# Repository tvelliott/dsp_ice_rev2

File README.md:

<html>
<b>480 MHz STM32H743 + ICE40 8K FGPA development board with 10/100 Ethernet interface 
<BR>
<BR><B>DSP_ICE_REV2
<BR>
<p>

<BR>
<BR>
Features
<BR>
<BR>
<PRE>
16-bit FSMC Interface between MCU <> FPGA  (DMA is supported)
3.5mm audio jack with high quality I2S DAC.  I2S can be generated from FPGA or MCU
FPGA clock input / PLL is fed from MCU MC0 output
Low Noise 3.3V supply
4 PMOD-style ports with 3.3V or 5V selectable voltages
10/100 Mbps Ethernet Interface  (DMA supported,  90+ Mbps IPerf results)
PDM Microphone connected to FPGA
</PRE>
  
<BR><BR>If you are looking for something similar, but with firmware / HDL code already available,  take a look at DSP_ICE Rev 1 here
<BR>https://github.com/tvelliott/dsp_ice 
</html>

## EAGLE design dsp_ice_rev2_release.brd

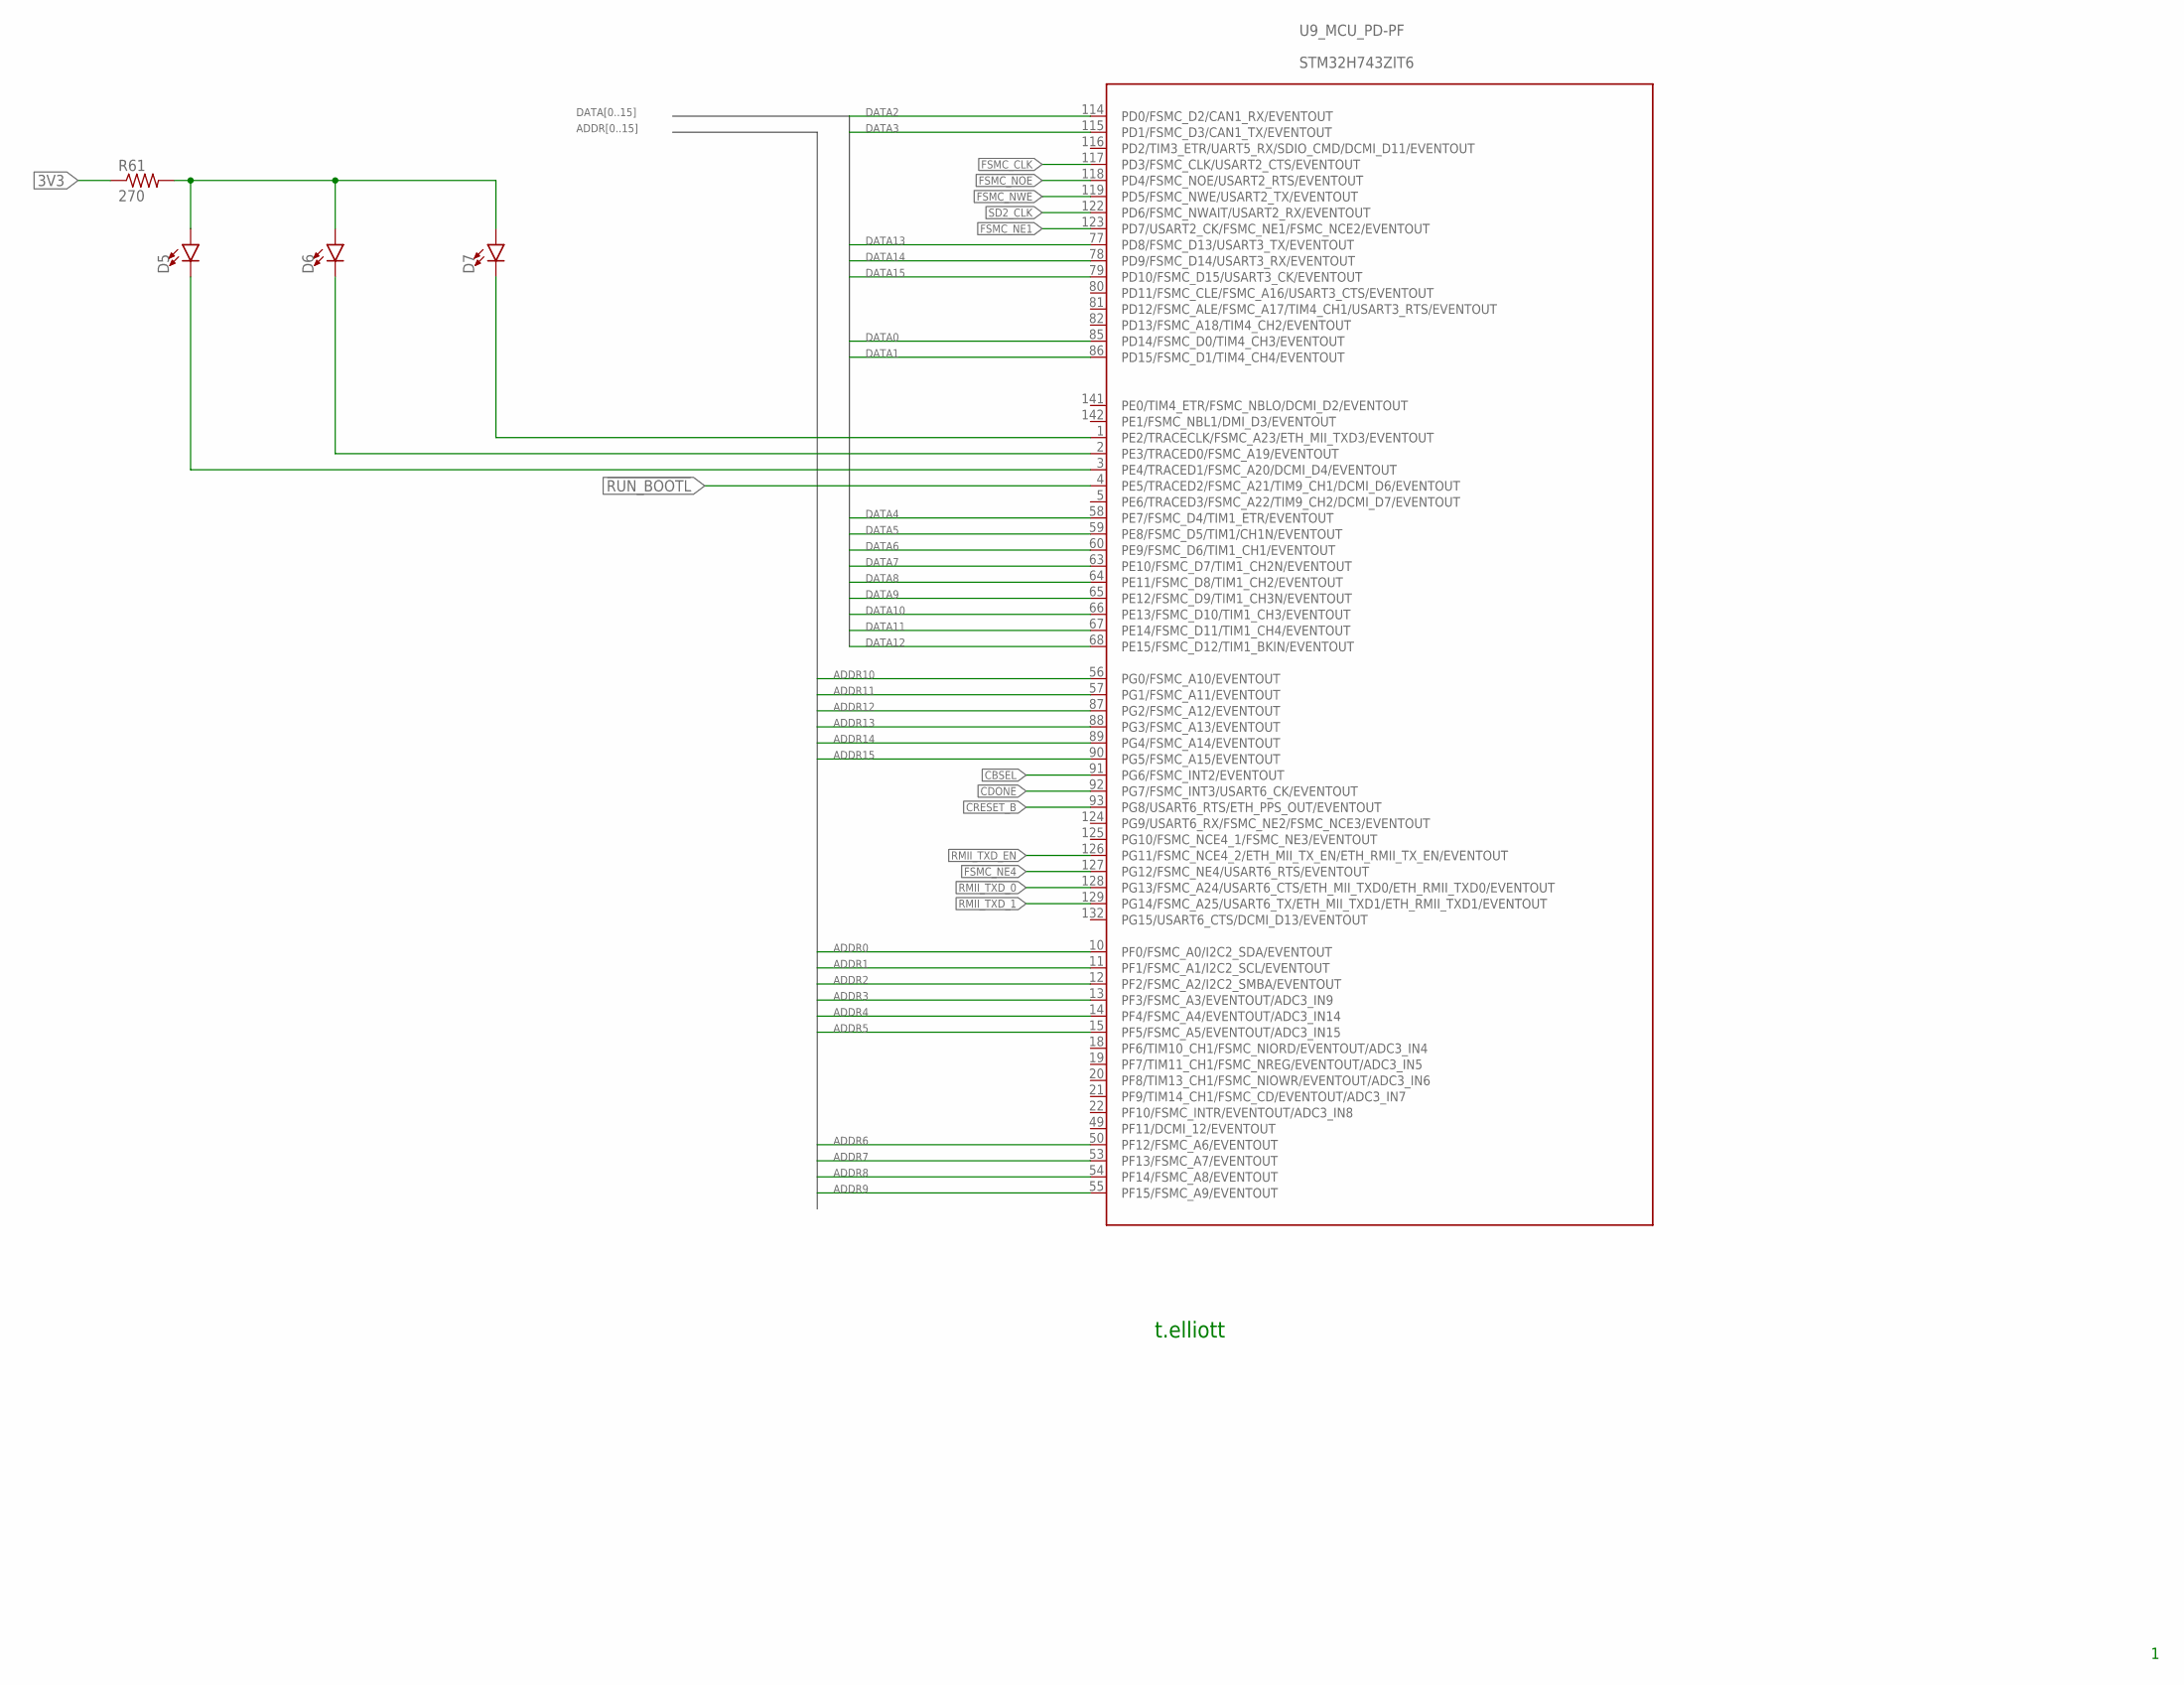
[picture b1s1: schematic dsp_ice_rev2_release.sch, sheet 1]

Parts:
D5, D6, D7: LED1206; LED-1206
R61: 270; R0603
U9: STM32H743ZIT6; STM32F407_144

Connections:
3V3: R61.1; also elsewhere on the board
!RUN_BOOTL: U9.4 (PE5/TRACED2/FSMC_A21/TIM9_CH1/DCMI_D6/E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); also elsewhere on the board
ADDR0: U9.10 (PF0/FSMC_A0/I2C2_SDA/EVENTOUT); also elsewhere on the board
ADDR1: U9.11 (PF1/FSMC_A1/I2C2_SCL/EVENTOUT); also elsewhere on the board
ADDR2: U9.12 (PF2/FSMC_A2/I2C2_SMBA/EVENTOUT); also elsewhere on the board
ADDR3: U9.13 (PF3/FSMC_A3/EVENTOUT/ADC3_IN9); also elsewhere on the board
ADDR4: U9.14 (PF4/FSMC_A4/EVENTOUT/ADC3_IN14); also elsewhere on the board
ADDR5: U9.15 (PF5/FSMC_A5/EVENTOUT/ADC3_IN15); also elsewhere on the board
ADDR6: U9.50 (PF12/FSMC_A6/EVENTOUT); also elsewhere on the board
ADDR7: U9.53 (PF13/FSMC_A7/EVENTOUT); also elsewhere on the board
ADDR8: U9.54 (PF14/FSMC_A8/EVENTOUT); also elsewhere on the board
ADDR9: U9.55 (PF15/FSMC_A9/EVENTOUT); also elsewhere on the board
ADDR10: U9.56 (PG0/FSMC_A10/EVENTOUT); also elsewhere on the board
ADDR11: U9.57 (PG1/FSMC_A11/EVENTOUT); also elsewhere on the board
ADDR12: U9.87 (PG2/FSMC_A12/EVENTOUT); also elsewhere on the board
ADDR13: U9.88 (PG3/FSMC_A13/EVENTOUT); also elsewhere on the board
ADDR14: U9.89 (PG4/FSMC_A14/EVENTOUT); also elsewhere on the board
ADDR15: U9.90 (PG5/FSMC_A15/EVENTOUT); also elsewhere on the board
CBSEL: U9.91 (PG6/FSMC_INT2/EVENTOUT); also elsewhere on the board
CDONE: U9.92 (PG7/FSMC_INT3/USART6_CK/EVENTOUT); also elsewhere on the board
CRESET_B: U9.93 (PG8/USART6_RTS/ETH_PPS_OUT/EVENTOUT); also elsewhere on the board
DATA0: U9.85 (PD14/FSMC_D0/TIM4_CH3/EVENTOUT); also elsewhere on the board
DATA1: U9.86 (PD15/FSMC_D1/TIM4_CH4/EVENTOUT); also elsewhere on the board
DATA2: U9.114 (PD0/FSMC_D2/CAN1_RX/EVENTOUT); also elsewhere on the board
DATA3: U9.115 (PD1/FSMC_D3/CAN1_TX/EVENTOUT); also elsewhere on the board
DATA4: U9.58 (PE7/FSMC_D4/TIM1_ETR/EVENTOUT); also elsewhere on the board
DATA5: U9.59 (PE8/FSMC_D5/TIM1/CH1N/EVENTOUT); also elsewhere on the board
DATA6: U9.60 (PE9/FSMC_D6/TIM1_CH1/EVENTOUT); also elsewhere on the board
DATA7: U9.63 (PE10/FSMC_D7/TIM1_CH2N/EVENTOUT); also elsewhere on the board
DATA8: U9.64 (PE11/FSMC_D8/TIM1_CH2/EVENTOUT); also elsewhere on the board
DATA9: U9.65 (PE12/FSMC_D9/TIM1_CH3N/EVENTOUT); also elsewhere on the board
DATA10: U9.66 (PE13/FSMC_D10/TIM1_CH3/EVENTOUT); also elsewhere on the board
DATA11: U9.67 (PE14/FSMC_D11/TIM1_CH4/EVENTOUT); also elsewhere on the board
DATA12: U9.68 (PE15/FSMC_D12/TIM1_BKIN/EVENTOUT); also elsewhere on the board
DATA13: U9.77 (PD8/FSMC_D13/USART3_TX/EVENTOUT); also elsewhere on the board
DATA14: U9.78 (PD9/FSMC_D14/USART3_RX/EVENTOUT); also elsewhere on the board
DATA15: U9.79 (PD10/FSMC_D15/USART3_CK/EVENTOUT); also elsewhere on the board
FSMC_CLK: U9.117 (PD3/FSMC_CLK/USART2_CTS/EVENTOUT); also elsewhere on the board
FSMC_NE1: U9.123 (PD7/USART2_CK/FSMC_NE1/FSMC_NCE2/EVENTO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); also elsewhere on the board
FSMC_NE4: U9.127 (PG12/FSMC_NE4/USART6_RTS/EVENTOUT); also elsewhere on the board
FSMC_NOE: U9.118 (PD4/FSMC_NOE/USART2_RTS/EVENTOUT); also elsewhere on the board
FSMC_NWE: U9.119 (PD5/FSMC_NWE/USART2_TX/EVENTOUT); also elsewhere on the board
unnamed: D5.A, D6.A, D7.A, R61.2
unnamed: D7.C, U9.1 (PE2/TRACECLK/FSMC_A23/ETH_MII_TXD3/EVEN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)
unnamed: D6.C, U9.2 (PE3/TRACED0/FSMC_A19/EVENTOUT)
unnamed: D5.C, U9.3 (PE4/TRACED1/FSMC_A20/DCMI_D4/EVENTOUT)
RMII_TXD_0: U9.128 (PG13/FSMC_A24/USART6_CTS/ETH_MII_TXD0/E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); also elsewhere on the board
RMII_TXD_1: U9.129 (PG14/FSMC_A25/USART6_TX/ETH_MII_TXD1/ET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); also elsewhere on the board
RMII_TXD_EN: U9.126 (PG11/FSMC_NCE4_2/ETH_MII_TX_EN/ETH_RMII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); also elsewhere on the board
SD2_CLK: U9.122 (PD6/FSMC_NWAIT/USART2_RX/EVENTOUT); also elsewhere on the board

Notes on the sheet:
t.elliott

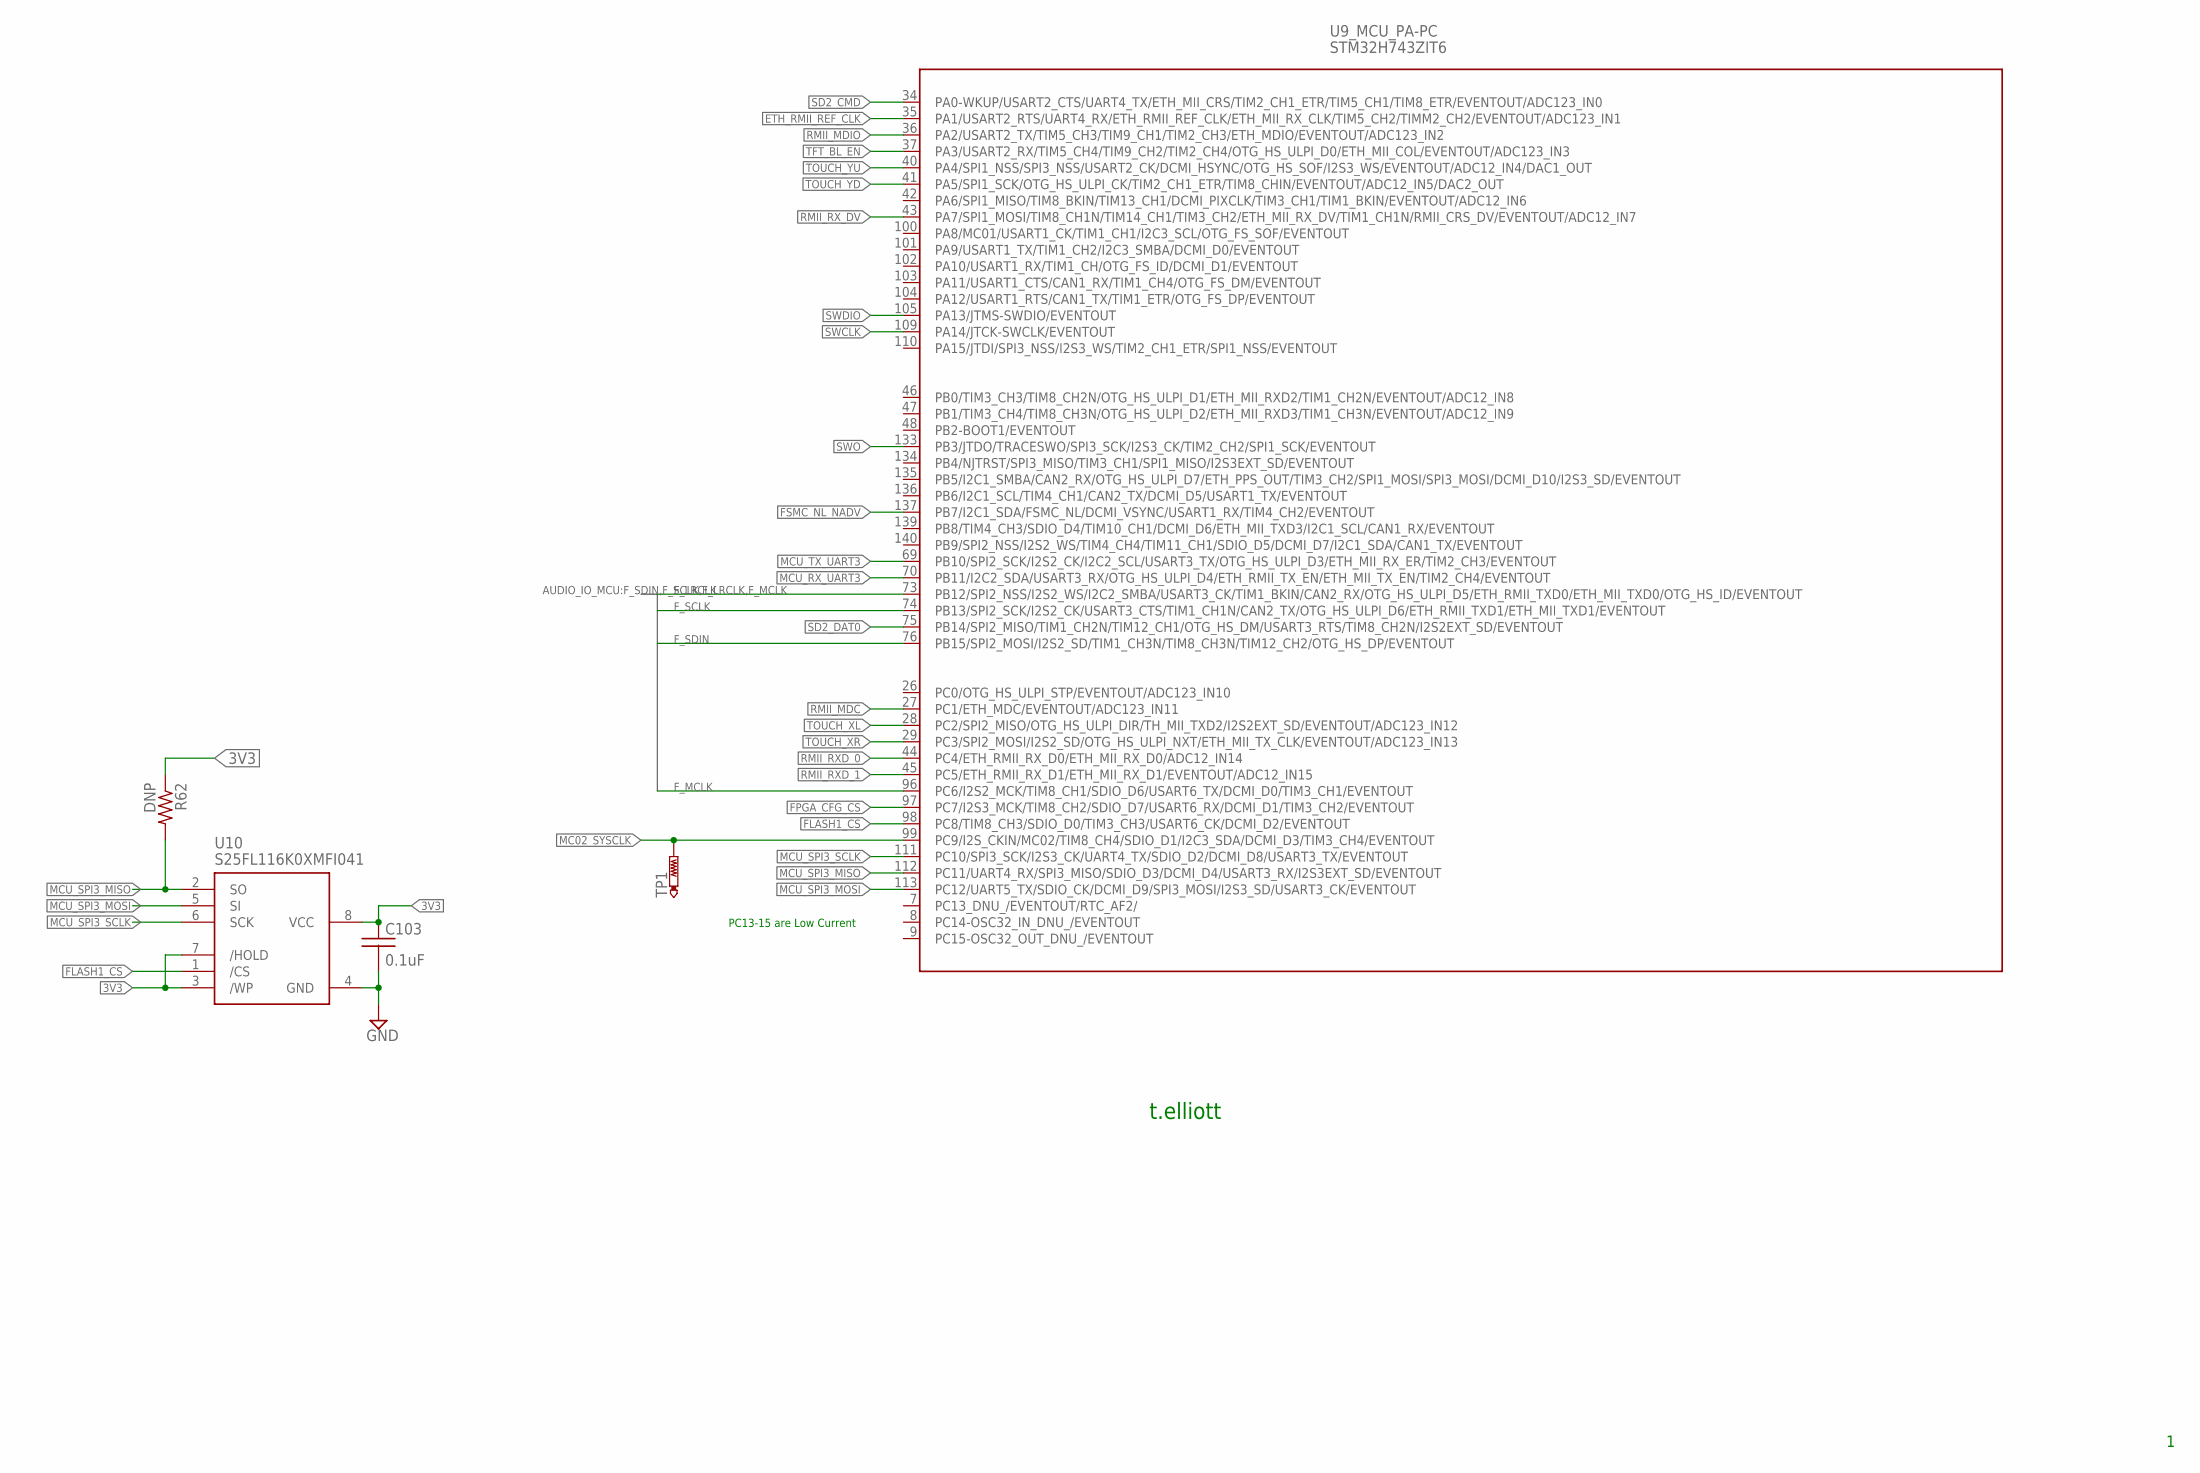
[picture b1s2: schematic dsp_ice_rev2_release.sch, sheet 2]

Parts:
C103: 0.1uF; C0603
R62: DNP; R0603
TP1: PTR1TP08R; TP08R
U9: STM32H743ZIT6; STM32F407_144
U10: S25FL116K0XMFI041; SO8

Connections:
3V3: C103.1, R62.1, U10.3 (/WP), U10.7 (/HOLD), U10.8 (VCC); also elsewhere on the board
ETH_RMII_REF_CLK: U9.35 (PA1/USART2_RTS/UART4_RX/ETH_RMII_REF_CL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); also elsewhere on the board
FLASH1_CS: U9.98 (PC8/TIM8_CH3/SDIO_D0/TIM3_CH3/USART6_CK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), U10.1 (/CS)
FPGA_CFG_CS: U9.97 (PC7/I2S3_MCK/TIM8_CH2/SDIO_D7/USART6_RX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); also elsewhere on the board
FSMC_NL_NADV: U9.137 (PB7/I2C1_SDA/FSMC_NL/DCMI_VSYNC/USART1_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); also elsewhere on the board
F_LRCLK: U9.73 (PB12/SPI2_NSS/I2S2_WS/I2C2_SMBA/USART3_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); also elsewhere on the board
F_MCLK: U9.96 (PC6/I2S2_MCK/TIM8_CH1/SDIO_D6/USART6_TX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); also elsewhere on the board
F_SCLK: U9.74 (PB13/SPI2_SCK/I2S2_CK/USART3_CTS/TIM1_C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); also elsewhere on the board
F_SDIN: U9.76 (PB15/SPI2_MOSI/I2S2_SD/TIM1_CH3N/TIM8_C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); also elsewhere on the board
GND: C103.2, U10.4 (GND); also elsewhere on the board
MC02_SYSCLK: TP1.TP, U9.99 (PC9/I2S_CKIN/MC02/TIM8_CH4/SDIO_D1/I2C3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); also elsewhere on the board
MCU_RX_UART3: U9.70 (PB11/I2C2_SDA/USART3_RX/OTG_HS_ULPI_D4/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); also elsewhere on the board
MCU_SPI3_MISO: R62.2, U9.112 (PC11/UART4_RX/SPI3_MISO/SDIO_D3/DCMI_D4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), U10.2 (SO); also elsewhere on the board
MCU_SPI3_MOSI: U9.113 (PC12/UART5_TX/SDIO_CK/DCMI_D9/SPI3_MOSI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), U10.5 (SI); also elsewhere on the board
MCU_SPI3_SCLK: U9.111 (PC10/SPI3_SCK/I2S3_CK/UART4_TX/SDIO_D2/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), U10.6 (SCK); also elsewhere on the board
MCU_TX_UART3: U9.69 (PB10/SPI2_SCK/I2S2_CK/I2C2_SCL/USART3_T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); also elsewhere on the board
RMII_MDC: U9.27 (PC1/ETH_MDC/EVENTOUT/ADC123_IN11); also elsewhere on the board
RMII_MDIO: U9.36 (PA2/USART2_TX/TIM5_CH3/TIM9_CH1/TIM2_CH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); also elsewhere on the board
RMII_RXD_0: U9.44 (PC4/ETH_RMII_RX_D0/ETH_MII_RX_D0/ADC12_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); also elsewhere on the board
RMII_RXD_1: U9.45 (PC5/ETH_RMII_RX_D1/ETH_MII_RX_D1/EVENTO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); also elsewhere on the board
RMII_RX_DV: U9.43 (PA7/SPI1_MOSI/TIM8_CH1N/TIM14_CH1/TIM3_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); also elsewhere on the board
SD2_CMD: U9.34 (PA0-WKUP/USART2_CTS/UART4_TX/ETH_MII_CR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); also elsewhere on the board
SD2_DAT0: U9.75 (PB14/SPI2_MISO/TIM1_CH2N/TIM12_CH1/OTG_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); also elsewhere on the board
SWCLK: U9.109 (PA14/JTCK-SWCLK/EVENTOUT); also elsewhere on the board
SWDIO: U9.105 (PA13/JTMS-SWDIO/EVENTOUT); also elsewhere on the board
SWO: U9.133 (PB3/JTDO/TRACESWO/SPI3_SCK/I2S3_CK/TIM2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); also elsewhere on the board
TFT_BL_EN: U9.37 (PA3/USART2_RX/TIM5_CH4/TIM9_CH2/TIM2_CH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); also elsewhere on the board
TOUCH_XL: U9.28 (PC2/SPI2_MISO/OTG_HS_ULPI_DIR/TH_MII_TX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); also elsewhere on the board
TOUCH_XR: U9.29 (PC3/SPI2_MOSI/I2S2_SD/OTG_HS_ULPI_NXT/E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); also elsewhere on the board
TOUCH_YD: U9.41 (PA5/SPI1_SCK/OTG_HS_ULPI_CK/TIM2_CH1_ET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); also elsewhere on the board
TOUCH_YU: U9.40 (PA4/SPI1_NSS/SPI3_NSS/USART2_CK/DCMI_HS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); also elsewhere on the board

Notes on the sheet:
PC13-15 are Low Current
t.elliott

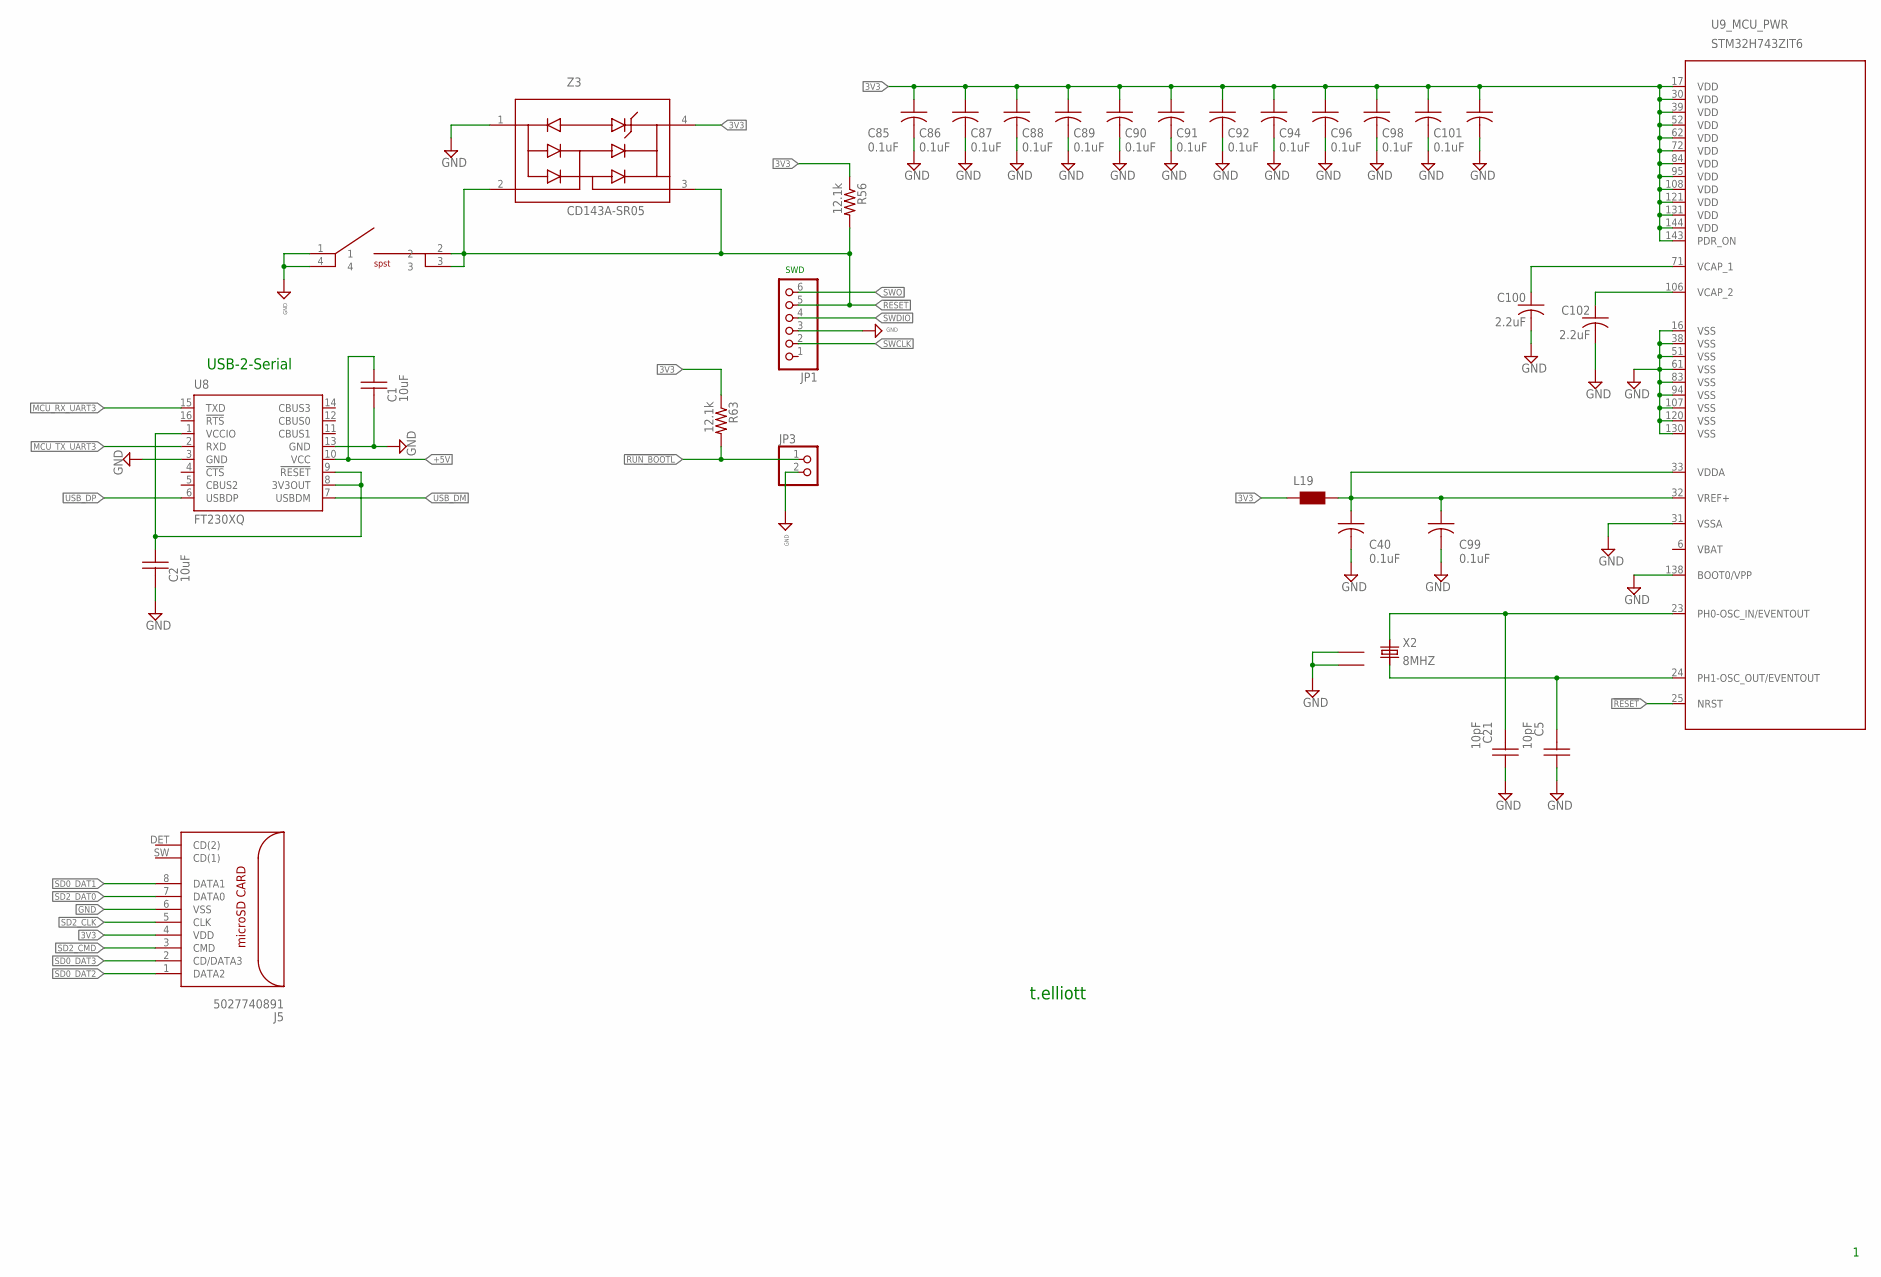
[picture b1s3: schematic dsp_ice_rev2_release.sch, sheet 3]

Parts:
C1, C2: 10uF; C0805
C5, C21: 10pF; C0402
C40, C85, C86, C87, C88, C89, C90, C91, C92, C94, C96, C98, C99, C101: 0.1uF; 0402
C100, C102: 2.2uF; C0805
J5: 5027740891; SD-502774-001
JP1: PINHD-1X6; 1X06
JP3: PINHD-1X2; 1X02
L19: WE-CBF_0603; 0603
R56, R63: 12.1k; R0603
SW3: HOKURIKU_KSM06_6X6MM_SWITCH1; TACTILE_6X6MM
U8: FT230XQ; QFN16
U9: STM32H743ZIT6; STM32F407_144
X2: 8MHZ; ECS-250-20-30B-DU_CRYSTAL
Z3: CD143A-SR05; SR2.8.TCT_1PRIMARY

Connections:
3V3: C85.1 (A), C86.1 (A), C87.1 (A), C88.1 (A), C89.1 (A), C90.1 (A), C91.1 (A), C92.1 (A), C94.1 (A), C96.1 (A), C98.1 (A), C101.1 (A), J5.4 (VDD), L19.1, R56.1, R63.1, U9.17 (VDD), U9.30 (VDD), U9.39 (VDD), U9.52 (VDD), U9.62 (VDD), U9.72 (VDD), U9.84 (VDD), U9.95 (VDD), U9.108 (VDD), U9.121 (VDD), U9.131 (VDD), U9.143 (PDR_ON), U9.144 (VDD), Z3.4 (REF); also elsewhere on the board
3V_ANALOG: C40.1 (A), C99.1 (A), L19.2, U9.32 (VREF+), U9.33 (VDDA)
20MHZ_REF: C21.2, U9.23 (PH0-OSC_IN/EVENTOUT), X2.1
!RESET: JP1.5, R56.2, SW3.2, SW3.3, U9.25 (NRST), Z3.2 (I/O), Z3.3 (I/O); also elsewhere on the board
!RUN_BOOTL: JP3.1, R63.2; also elsewhere on the board
+5V: C1.1, U8.10 (VCC); also elsewhere on the board
GND: C1.2, C2.2, C5.1, C21.1, C40.2 (C), C85.2 (C), C86.2 (C), C87.2 (C), C88.2 (C), C89.2 (C), C90.2 (C), C91.2 (C), C92.2 (C), C94.2 (C), C96.2 (C), C98.2 (C), C99.2 (C), C100.2, C101.2 (C), C102.2, J5.6 (VSS), JP1.3, JP3.2, SW3.1, SW3.4, U8.3 (GND), U8.13 (GND), U9.16 (VSS), U9.31 (VSSA), U9.38 (VSS), U9.51 (VSS), U9.61 (VSS), U9.83 (VSS), U9.94 (VSS), U9.107 (VSS), U9.120 (VSS), U9.130 (VSS), U9.138 (BOOT0/VPP), X2.GND@1 (1), X2.GND@2 (2), Z3.1 (GND); also elsewhere on the board
MCU_RX_UART3: U8.15 (TXD); also elsewhere on the board
MCU_TX_UART3: U8.2 (RXD); also elsewhere on the board
unnamed: C102.1, U9.106 (VCAP_2)
unnamed: C2.1, U8.1 (VCCIO), U8.8 (3V3OUT), U8.9 (!RESET)
unnamed: C100.1, U9.71 (VCAP_1)
SD0_DAT1: J5.8 (DATA1)
SD0_DAT2: J5.1 (DATA2)
SD0_DAT3: J5.2 (CD/DATA3)
SD2_CLK: J5.5 (CLK); also elsewhere on the board
SD2_CMD: J5.3 (CMD); also elsewhere on the board
SD2_DAT0: J5.7 (DATA0); also elsewhere on the board
SWCLK: JP1.2; also elsewhere on the board
SWDIO: JP1.4; also elsewhere on the board
SWO: JP1.6; also elsewhere on the board
USB_DM: U8.7 (USBDM); also elsewhere on the board
USB_DP: U8.6 (USBDP); also elsewhere on the board
X2: C5.2, U9.24 (PH1-OSC_OUT/EVENTOUT), X2.3

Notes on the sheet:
t.elliott
SWD
USB-2-Serial

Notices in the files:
parts and their libraries:
cirrus-3: Copyright (C) 2005 by Bob Starr, rtzaudio@mindspring.com
SparkFun-LED: Licensing: Creative Commons ShareAlike 4.0 International - https://creativecommons.org/licenses/by-sa/4.0
